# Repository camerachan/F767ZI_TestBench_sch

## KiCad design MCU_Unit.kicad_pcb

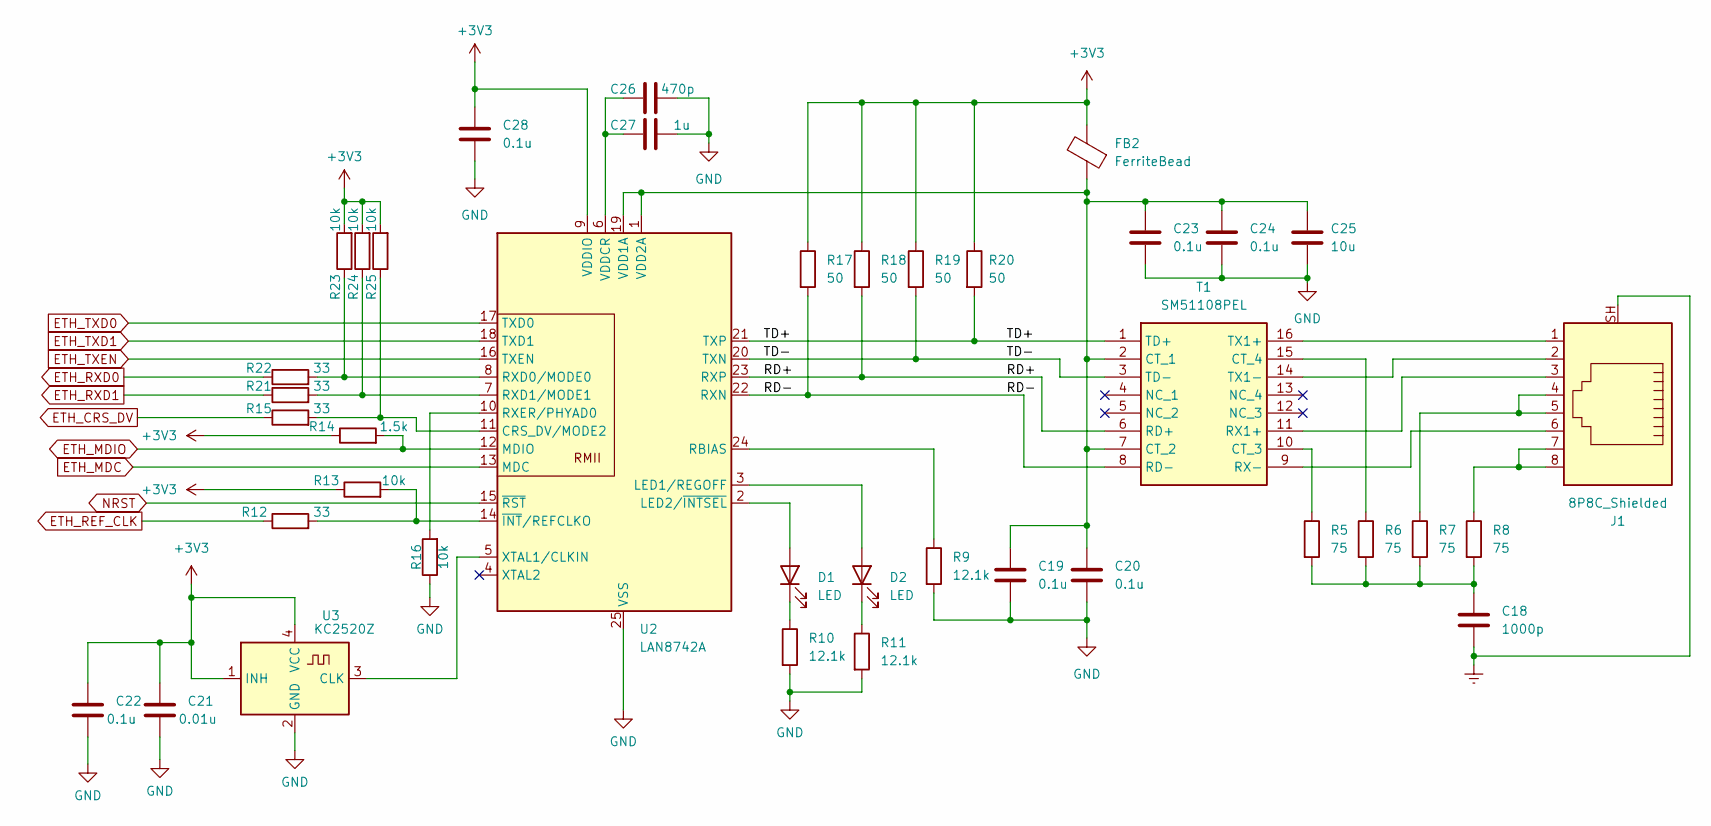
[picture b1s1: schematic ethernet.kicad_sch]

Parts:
C18: 1000p; C_1206_3216Metric_Pad1.33x1.80mm_HandSolder
C19, C20, C22, C23, C24: 0.1u; C_0603_1608Metric_Pad1.08x0.95mm_HandSolder
C21: 0.01u; C_0603_1608Metric_Pad1.08x0.95mm_HandSolder
C25: 10u; C_1206_3216Metric_Pad1.33x1.80mm_HandSolder
C26: 470p; C_0603_1608Metric_Pad1.08x0.95mm_HandSolder
C27: 1u; C_0603_1608Metric_Pad1.08x0.95mm_HandSolder
C28: 0.1u; C_0402_1005Metric_Pad0.74x0.62mm_HandSolder
D1, D2: LED; LED_0603_1608Metric_Pad1.05x0.95mm_HandSolder
FB2: FerriteBead; L_0603_1608Metric_Pad1.05x0.95mm_HandSolder
J1: 8P8C_Shielded; RJ45_Amphenol_RJHSE5380
R5, R6, R7, R8: 75; R_0603_1608Metric_Pad0.98x0.95mm_HandSolder
R9, R10, R11: 12.1k; R_0603_1608Metric_Pad0.98x0.95mm_HandSolder
R12, R15, R21, R22: 33; R_0603_1608Metric_Pad0.98x0.95mm_HandSolder
R13, R16, R23, R24, R25: 10k; R_0603_1608Metric_Pad0.98x0.95mm_HandSolder
R14: 1.5k; R_0603_1608Metric_Pad0.98x0.95mm_HandSolder
R17, R18, R19, R20: 50; R_0603_1608Metric_Pad0.98x0.95mm_HandSolder
T1: SM51108PEL; SOIC127P930X590-16N; Mouser Part Number 652-SM51108PEL
U2: LAN8742A; VQFN-24-1EP_4x4mm_P0.5mm_EP2.45x2.45mm
U3: KC2520Z; Oscillator_SMD_Kyocera_KC2520Z-4Pin_2.5x2.0mm

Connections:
+3V3: C21.1, C22.1, C28.1, FB2.2, R13.1, R14.1, R17.1, R18.1, R19.1, R20.1, R23.2, R24.2, R25.2, U2.9 (VDDIO), U3.1 (INH), U3.4 (VCC); also elsewhere on the board
/Ethernet/RD+: R18.2, T1.6 (RD+), U2.23 (RXP)
/Ethernet/RD-: R17.2, T1.8 (RD-), U2.22 (RXN)
/Ethernet/TD+: R20.2, T1.1 (TD+), U2.21 (TXP)
/Ethernet/TD-: R19.2, T1.3 (TD-), U2.20 (TXN)
ETH_CRS_DV: R15.1; also elsewhere on the board
ETH_MDC: U2.13 (MDC); also elsewhere on the board
ETH_MDIO: R14.2, U2.12 (MDIO); also elsewhere on the board
ETH_REF_CLK: R12.1; also elsewhere on the board
ETH_RXD0: R22.1; also elsewhere on the board
ETH_RXD1: R21.1; also elsewhere on the board
ETH_TXD0: U2.17 (TXD0); also elsewhere on the board
ETH_TXD1: U2.18 (TXD1); also elsewhere on the board
ETH_TXEN: U2.16 (TXEN); also elsewhere on the board
Earth: C18.2, J1.SH
GND: C19.2, C20.2, C21.2, C22.2, C23.2, C24.2, C25.2, C26.2, C27.2, C28.2, R9.2, R10.2, R11.2, R16.1, U2.25 (VSS), U3.2 (GND); also elsewhere on the board
NRST: U2.15 (~RST); also elsewhere on the board
unnamed: C18.1, R5.2, R6.2, R7.2, R8.2
unnamed: D1.2 (A), U2.2 (LED2/~INTSEL)
unnamed: D1.1 (K), R10.1
unnamed: D2.2 (A), U2.3 (LED1/REGOFF)
unnamed: D2.1 (K), R11.1
unnamed: J1.4, J1.5, R7.1
unnamed: J1.7, J1.8, R8.1
unnamed: C19.1, C20.1, C23.1, C24.1, C25.1, FB2.1, T1.2 (CT_1), T1.7 (CT_2), U2.1 (VDD2A), U2.19 (VDD1A)
unnamed: R5.1, T1.10 (CT_3)
unnamed: R6.1, T1.15 (CT_4)
unnamed: J1.3, T1.11 (RX1+)
unnamed: J1.6, T1.9 (RX-)
unnamed: J1.1, T1.16 (TX1+)
unnamed: J1.2, T1.14 (TX1-)
unnamed: R15.2, R25.1, U2.11 (CRS_DV/MODE2)
unnamed: R9.1, U2.24 (RBIAS)
unnamed: R22.2, R23.1, U2.8 (RXD0/MODE0)
unnamed: R21.2, R24.1, U2.7 (RXD1/MODE1)
unnamed: R16.2, U2.10 (RXER/PHYAD0)
unnamed: C26.1, C27.1, U2.6 (VDDCR)
unnamed: U2.5 (XTAL1/CLKIN), U3.3 (CLK)
unnamed: R12.2, R13.2, U2.14 (~INT/REFCLKO)

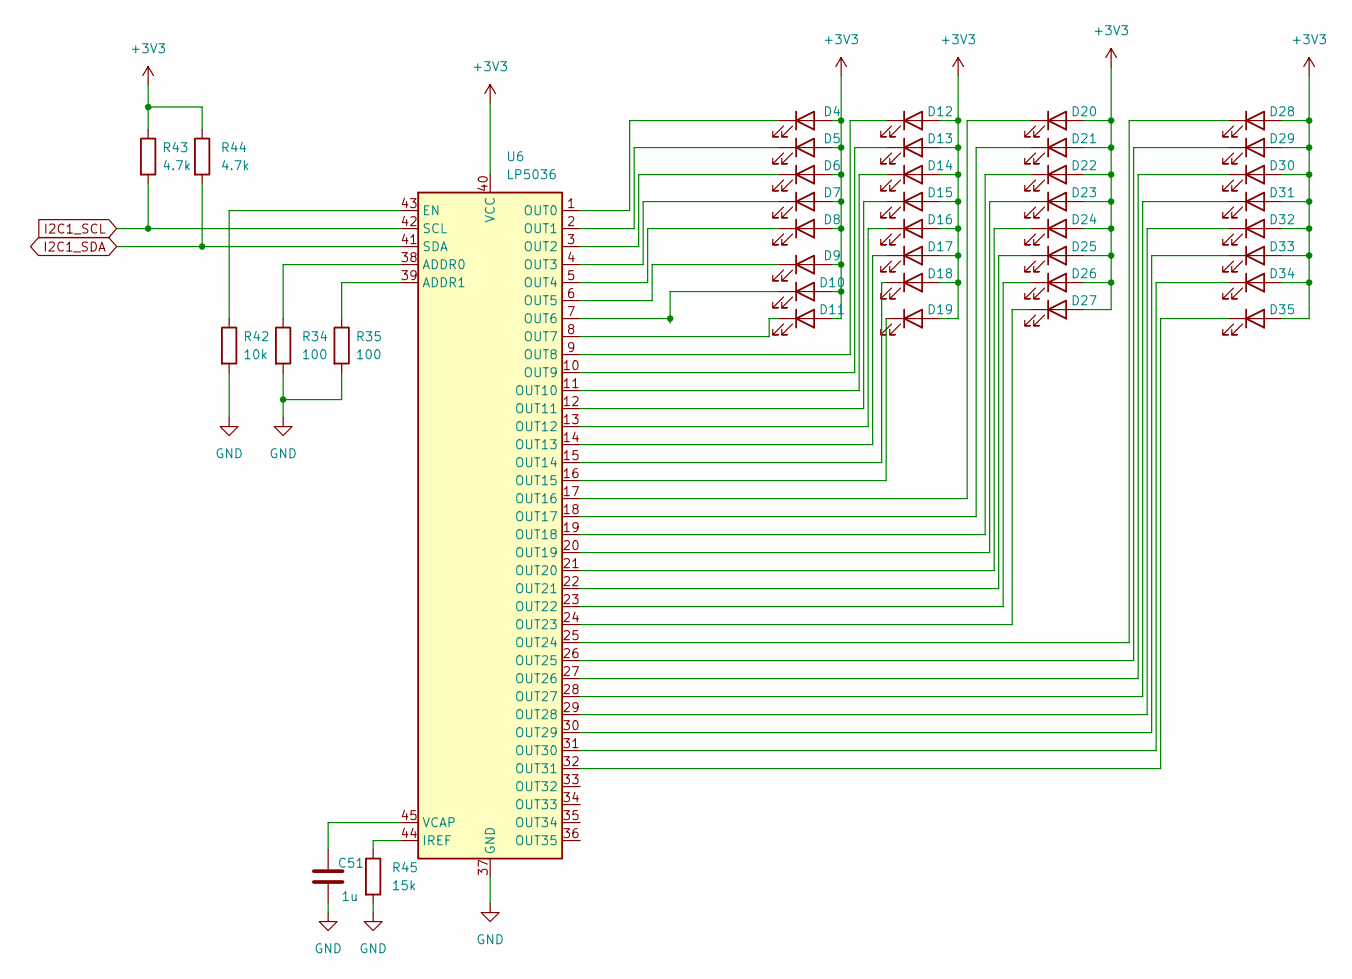
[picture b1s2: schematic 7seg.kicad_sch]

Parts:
C51: 1u; C_0603_1608Metric_Pad1.08x0.95mm_HandSolder
D4, D5, D6, D7, D8, D9, D10, D11, D12, D13, D14, D15, D16, D17, D18, D19, D20, D21, D22, D23, D24, D25, D26, D27, D28, D29, D30, D31, D32, D33, D34, D35: LED; LED_0402_1005Metric_Pad0.77x0.64mm_HandSolder
R34, R35: 100; R_0603_1608Metric_Pad0.98x0.95mm_HandSolder
R42: 10k; R_0603_1608Metric_Pad0.98x0.95mm_HandSolder
R43, R44: 4.7k; R_0603_1608Metric_Pad0.98x0.95mm_HandSolder
R45: 15k; R_0603_1608Metric_Pad0.98x0.95mm_HandSolder
U6: LP5036; VQFN-46-1EP_5x6mm_P0.4mm_EP2.8x3.8mm

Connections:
+3V3: D4.2 (A), D5.2 (A), D6.2 (A), D7.2 (A), D8.2 (A), D9.2 (A), D10.2 (A), D11.2 (A), D12.2 (A), D13.2 (A), D14.2 (A), D15.2 (A), D16.2 (A), D17.2 (A), D18.2 (A), D19.2 (A), D20.2 (A), D21.2 (A), D22.2 (A), D23.2 (A), D24.2 (A), D25.2 (A), D26.2 (A), D27.2 (A), D28.2 (A), D29.2 (A), D30.2 (A), D31.2 (A), D32.2 (A), D33.2 (A), D34.2 (A), D35.2 (A), R43.1, R44.1, U6.40 (VCC); also elsewhere on the board
GND: C51.2, R34.2, R35.2, R42.2, R45.2, U6.37 (GND), U6.46 (GND), U6.47 (GND); also elsewhere on the board
I2C1_SCL: R43.2, U6.42 (SCL); also elsewhere on the board
I2C1_SDA: R44.2, U6.41 (SDA); also elsewhere on the board
unnamed: D4.1 (K), U6.1 (OUT0)
unnamed: D5.1 (K), U6.2 (OUT1)
unnamed: D6.1 (K), U6.3 (OUT2)
unnamed: D7.1 (K), U6.4 (OUT3)
unnamed: D8.1 (K), U6.5 (OUT4)
unnamed: D9.1 (K), U6.6 (OUT5)
unnamed: D10.1 (K), U6.7 (OUT6)
unnamed: D11.1 (K), U6.8 (OUT7)
unnamed: D12.1 (K), U6.9 (OUT8)
unnamed: D13.1 (K), U6.10 (OUT9)
unnamed: D14.1 (K), U6.11 (OUT10)
unnamed: D15.1 (K), U6.12 (OUT11)
unnamed: D16.1 (K), U6.13 (OUT12)
unnamed: D17.1 (K), U6.14 (OUT13)
unnamed: D18.1 (K), U6.15 (OUT14)
unnamed: D19.1 (K), U6.16 (OUT15)
unnamed: D20.1 (K), U6.17 (OUT16)
unnamed: D21.1 (K), U6.18 (OUT17)
unnamed: D22.1 (K), U6.19 (OUT18)
unnamed: D23.1 (K), U6.20 (OUT19)
unnamed: D24.1 (K), U6.21 (OUT20)
unnamed: D25.1 (K), U6.22 (OUT21)
unnamed: D26.1 (K), U6.23 (OUT22)
unnamed: D27.1 (K), U6.24 (OUT23)
unnamed: D28.1 (K), U6.25 (OUT24)
unnamed: D29.1 (K), U6.26 (OUT25)
unnamed: D30.1 (K), U6.27 (OUT26)
unnamed: D31.1 (K), U6.28 (OUT27)
unnamed: D32.1 (K), U6.29 (OUT28)
unnamed: D33.1 (K), U6.30 (OUT29)
unnamed: D34.1 (K), U6.31 (OUT30)
unnamed: D35.1 (K), U6.32 (OUT31)
unnamed: R34.1, U6.38 (ADDR0)
unnamed: R35.1, U6.39 (ADDR1)
unnamed: R42.1, U6.43 (EN)
unnamed: R45.1, U6.44 (IREF)
unnamed: C51.1, U6.45 (VCAP)

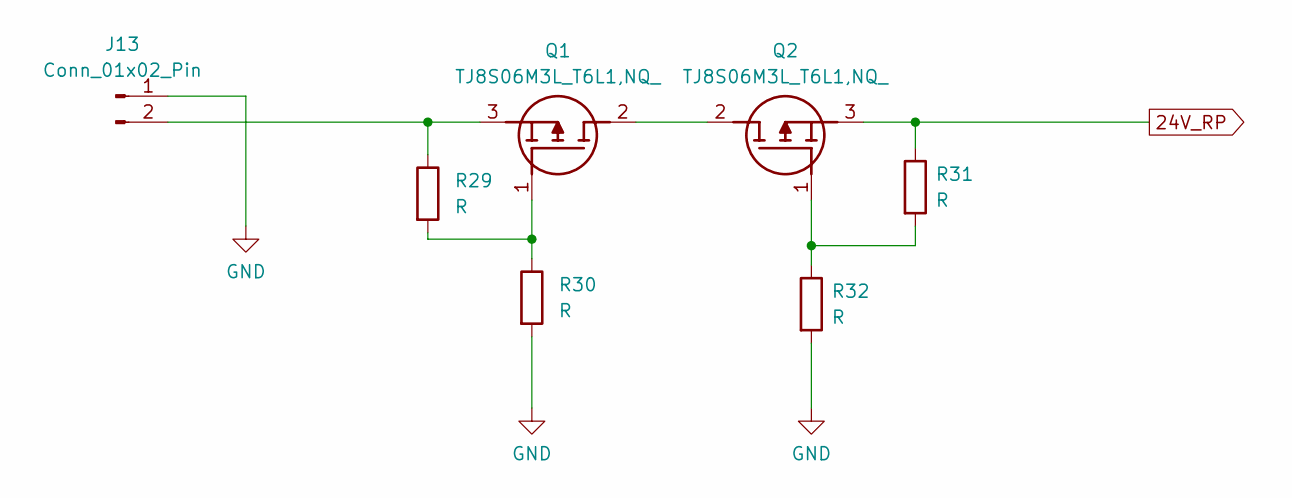
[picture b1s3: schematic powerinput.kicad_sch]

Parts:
J13: Conn_01x02_Pin; AMASS_XT30PW-M_1x02_P2.50mm_Horizontal
Q1, Q2: TJ8S06M3L_T6L1,NQ_; TJ8S06M3LT6L1NQ; Mouser Part Number 757-TJ8S06M3LT6L1NQ
R29, R30, R31, R32: R; R_0603_1608Metric_Pad0.98x0.95mm_HandSolder

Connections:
24V_RP: Q2.3 (S), R31.1; also elsewhere on the board
GND: J13.1, R30.2, R32.2; also elsewhere on the board
unnamed: J13.2, Q1.3 (S), R29.1
unnamed: Q1.2 (D), Q2.2 (D)
unnamed: Q1.1 (G), R29.2, R30.1
unnamed: Q2.1 (G), R31.2, R32.1

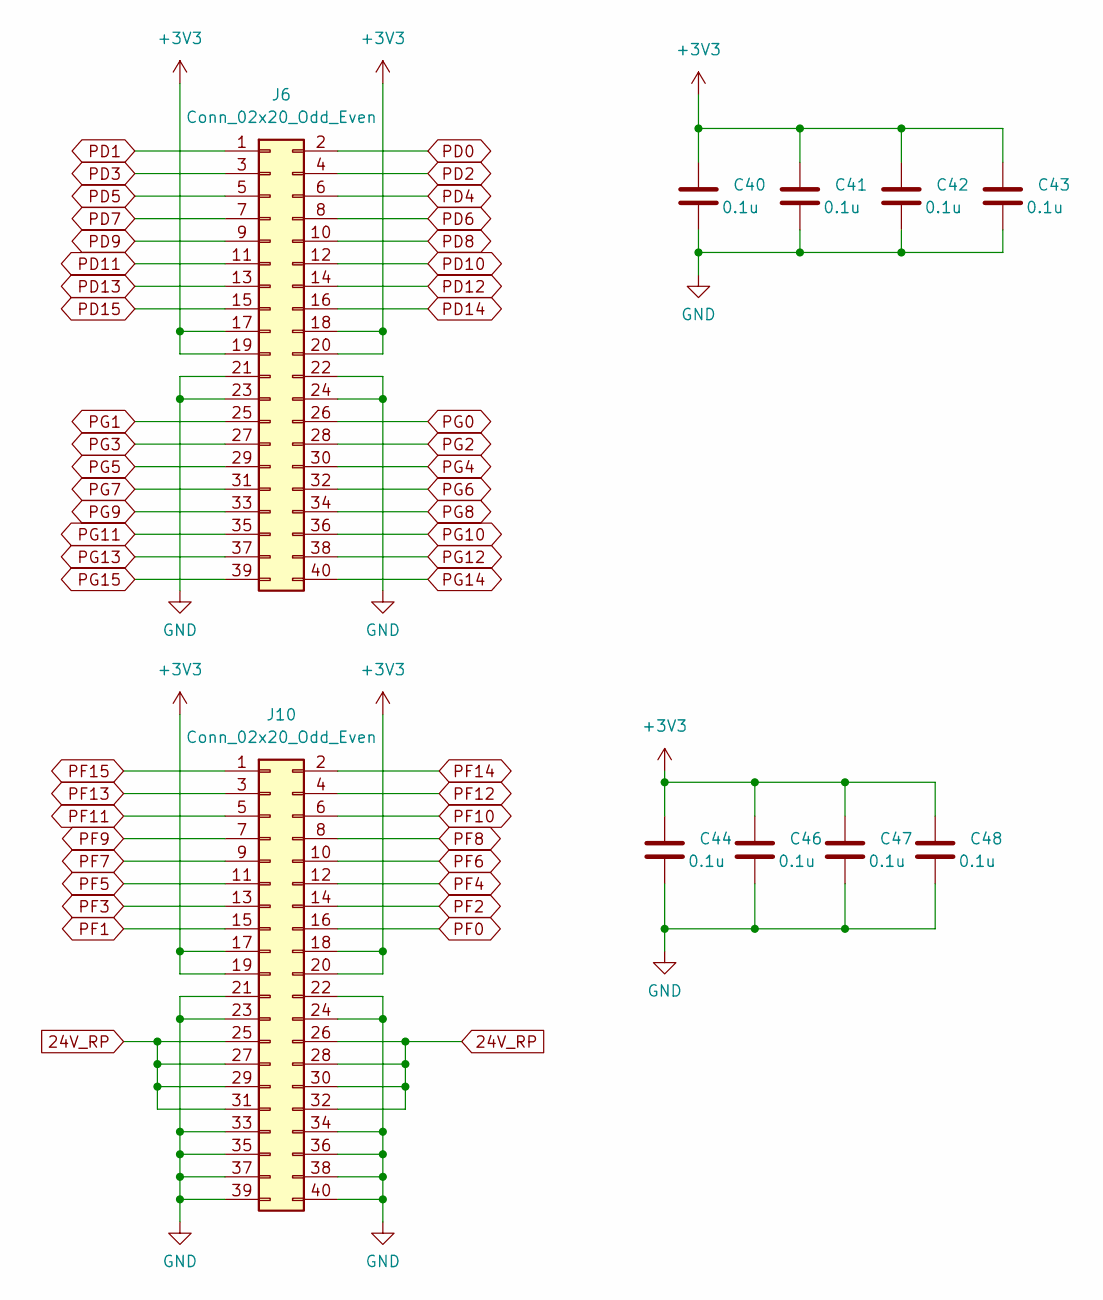
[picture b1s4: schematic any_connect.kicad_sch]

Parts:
C40, C41, C42, C43, C44, C46, C47, C48: 0.1u; C_0603_1608Metric_Pad1.08x0.95mm_HandSolder
J6, J10: Conn_02x20_Odd_Even; PinSocket_2x20_P2.54mm_Vertical

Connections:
24V_RP: J10.25, J10.26, J10.27, J10.28, J10.29, J10.30, J10.31, J10.32; also elsewhere on the board
+3V3: C40.1, C41.1, C42.1, C43.1, C44.1, C46.1, C47.1, C48.1, J6.17, J6.18, J6.19, J6.20, J10.17, J10.18, J10.19, J10.20; also elsewhere on the board
GND: C40.2, C41.2, C42.2, C43.2, C44.2, C46.2, C47.2, C48.2, J6.21, J6.22, J6.23, J6.24, J10.21, J10.22, J10.23, J10.24, J10.33, J10.34, J10.35, J10.36, J10.37, J10.38, J10.39, J10.40; also elsewhere on the board
PD0: J6.2; also elsewhere on the board
PD1: J6.1; also elsewhere on the board
PD2: J6.4; also elsewhere on the board
PD3: J6.3; also elsewhere on the board
PD4: J6.6; also elsewhere on the board
PD5: J6.5; also elsewhere on the board
PD6: J6.8; also elsewhere on the board
PD7: J6.7; also elsewhere on the board
PD8: J6.10; also elsewhere on the board
PD9: J6.9; also elsewhere on the board
PD10: J6.12; also elsewhere on the board
PD11: J6.11; also elsewhere on the board
PD12: J6.14; also elsewhere on the board
PD13: J6.13; also elsewhere on the board
PD14: J6.16; also elsewhere on the board
PD15: J6.15; also elsewhere on the board
PF0: J10.16; also elsewhere on the board
PF1: J10.15; also elsewhere on the board
PF2: J10.14; also elsewhere on the board
PF3: J10.13; also elsewhere on the board
PF4: J10.12; also elsewhere on the board
PF5: J10.11; also elsewhere on the board
PF6: J10.10; also elsewhere on the board
PF7: J10.9; also elsewhere on the board
PF8: J10.8; also elsewhere on the board
PF9: J10.7; also elsewhere on the board
PF10: J10.6; also elsewhere on the board
PF11: J10.5; also elsewhere on the board
PF12: J10.4; also elsewhere on the board
PF13: J10.3; also elsewhere on the board
PF14: J10.2; also elsewhere on the board
PF15: J10.1; also elsewhere on the board
PG0: J6.26; also elsewhere on the board
PG1: J6.25; also elsewhere on the board
PG2: J6.28; also elsewhere on the board
PG3: J6.27; also elsewhere on the board
PG4: J6.30; also elsewhere on the board
PG5: J6.29; also elsewhere on the board
PG6: J6.32; also elsewhere on the board
PG7: J6.31; also elsewhere on the board
PG8: J6.34; also elsewhere on the board
PG9: J6.33; also elsewhere on the board
PG10: J6.36; also elsewhere on the board
PG11: J6.35; also elsewhere on the board
PG12: J6.38; also elsewhere on the board
PG13: J6.37; also elsewhere on the board
PG14: J6.40; also elsewhere on the board
PG15: J6.39; also elsewhere on the board

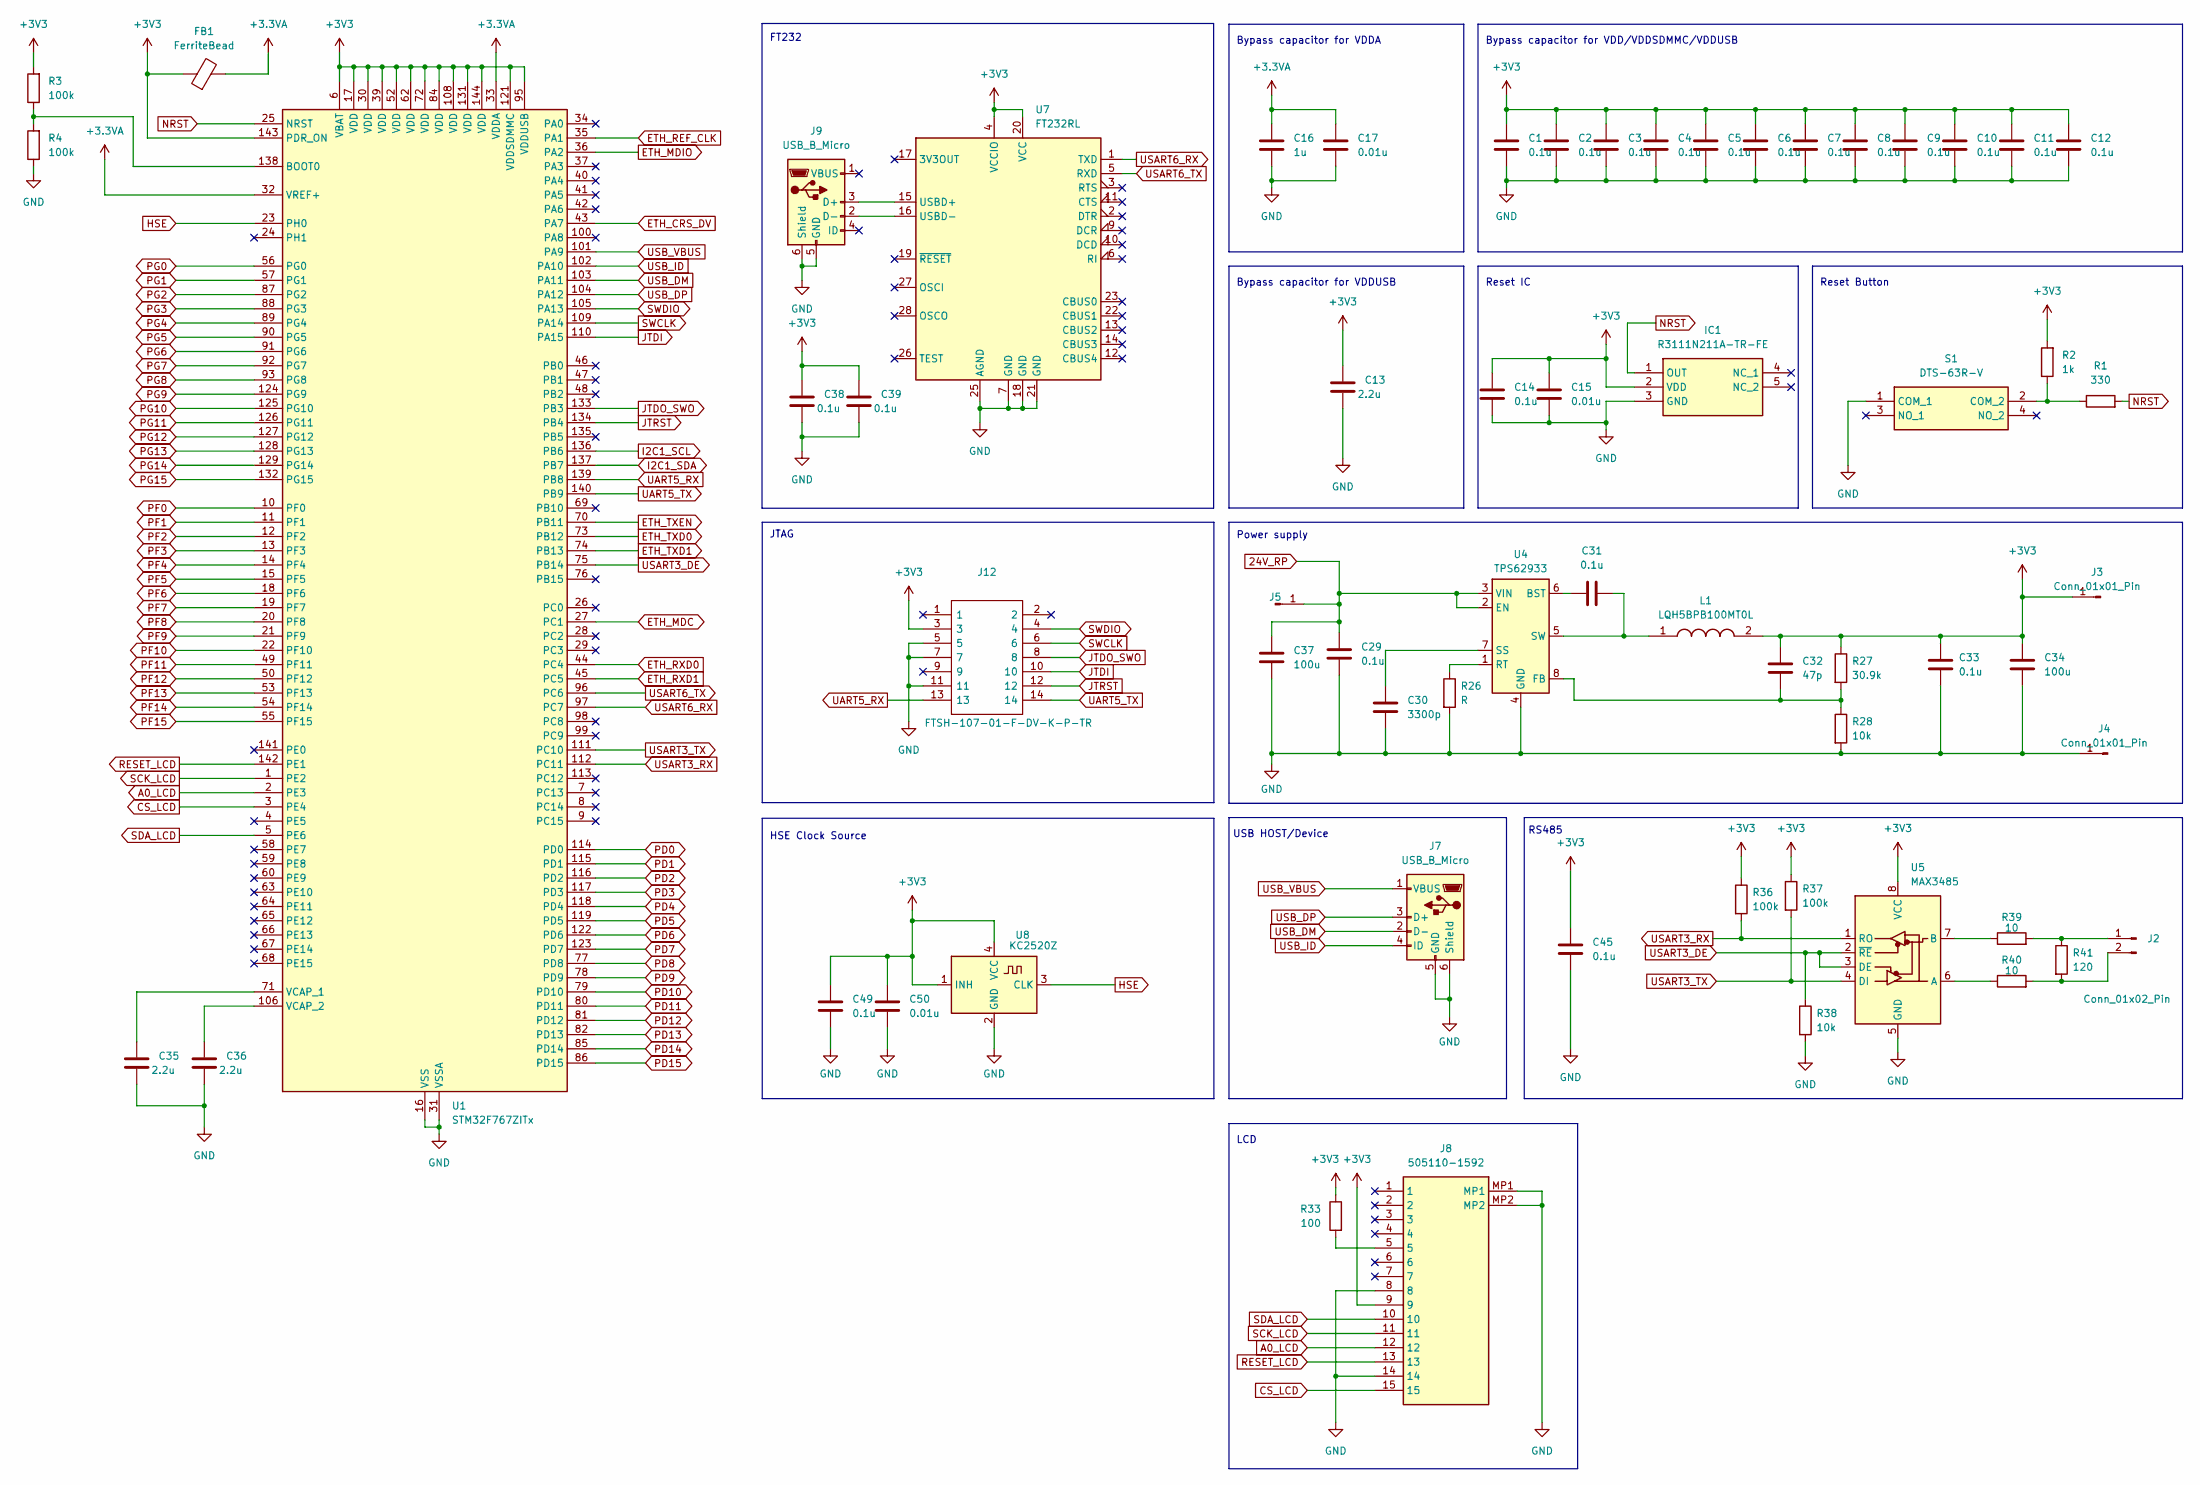
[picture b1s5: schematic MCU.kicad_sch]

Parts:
C1, C2, C3, C4, C5, C6, C7, C8, C9, C10, C11, C12, C14, C49: 0.1u; C_0402_1005Metric_Pad0.74x0.62mm_HandSolder
C13, C35, C36: 2.2u; C_0603_1608Metric_Pad1.08x0.95mm_HandSolder
C15, C17, C50: 0.01u; C_0402_1005Metric_Pad0.74x0.62mm_HandSolder
C16: 1u; C_0402_1005Metric_Pad0.74x0.62mm_HandSolder
C29, C31, C33, C38, C39, C45: 0.1u; C_0603_1608Metric_Pad1.08x0.95mm_HandSolder
C30: 3300p; C_0603_1608Metric_Pad1.08x0.95mm_HandSolder
C32: 47p; C_0603_1608Metric_Pad1.08x0.95mm_HandSolder
C34, C37: 100u; C_Elec_8x10.2
FB1: FerriteBead; L_0603_1608Metric_Pad1.05x0.95mm_HandSolder
IC1: R3111N211A-TR-FE; SOT95P280X130-5N; Mouser Part Number 848-R3111N211A-TR-FE
J2: Conn_01x02_Pin; JST_XH_B2B-XH-AM_1x02_P2.50mm_Vertical
J3, J4, J5: Conn_01x01_Pin; PinHeader_1x01_P2.54mm_Vertical
J7, J9: USB_B_Micro; USB_Mini-B_Wuerth_65100516121_Horizontal
J8: 505110-1592; 5051101592; Mouser Part Number 538-505110-1592
J12: FTSH-107-01-F-DV-K-P-TR; FTSH-107-XX-YYY-DV-K-P-TR; Mouser Part Number 200-FTSH10701FDVKPTR
L1: LQH5BPB100MT0L; Mouser Part Number 81-LQH5BPB100MT0L
R1: 330; R_0603_1608Metric_Pad0.98x0.95mm_HandSolder
R2: 1k; R_0603_1608Metric_Pad0.98x0.95mm_HandSolder
R3, R4, R36, R37: 100k; R_0603_1608Metric_Pad0.98x0.95mm_HandSolder
R26: R; R_0603_1608Metric_Pad0.98x0.95mm_HandSolder
R27: 30.9k; R_0603_1608Metric_Pad0.98x0.95mm_HandSolder
R28, R38: 10k; R_0603_1608Metric_Pad0.98x0.95mm_HandSolder
R33: 100; R_0603_1608Metric_Pad0.98x0.95mm_HandSolder
R39, R40: 10; R_0603_1608Metric_Pad0.98x0.95mm_HandSolder
R41: 120; R_Axial_DIN0207_L6.3mm_D2.5mm_P10.16mm_Horizontal
S1: DTS-63R-V; DTS63RV; Mouser Part Number 113-DTS63RV
U1: STM32F767ZITx; LQFP-144_20x20mm_P0.5mm
U4: TPS62933; SOT-583-8
U5: MAX3485; SOIC-8_3.9x4.9mm_P1.27mm
U7: FT232RL; SSOP-28_5.3x10.2mm_P0.65mm
U8: KC2520Z; Oscillator_SMD_Kyocera_KC2520Z-4Pin_2.5x2.0mm

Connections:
24V_RP: C29.1, C37.1, J5.1, U4.2 (EN), U4.3 (VIN); also elsewhere on the board
+3.3VA: C16.1, C17.1, FB1.2, U1.32 (VREF+), U1.33 (VDDA)
+3V3: C1.1, C2.1, C3.1, C4.1, C5.1, C6.1, C7.1, C8.1, C9.1, C10.1, C11.1, C12.1, C13.1, C14.1, C15.1, C32.1, C33.1, C34.1, C38.1, C39.1, C45.1, C49.1, C50.1, FB1.1, IC1.2 (VDD), J3.1, J8.9, J12.3, L1.2, R2.2, R3.2, R27.1, R33.1, R36.1, R37.1, U1.6 (VBAT), U1.17 (VDD), U1.30 (VDD), U1.39 (VDD), U1.52 (VDD), U1.62 (VDD), U1.72 (VDD), U1.84 (VDD), U1.95 (VDDUSB), U1.108 (VDD), U1.121 (VDDSDMMC), U1.131 (VDD), U1.143 (PDR_ON), U1.144 (VDD), U5.8 (VCC), U7.4 (VCCIO), U7.20 (VCC), U8.1 (INH), U8.4 (VCC); also elsewhere on the board
A0_LCD: J8.12, U1.2 (PE3)
CS_LCD: J8.15, U1.3 (PE4)
ETH_CRS_DV: U1.43 (PA7); also elsewhere on the board
ETH_MDC: U1.27 (PC1); also elsewhere on the board
ETH_MDIO: U1.36 (PA2); also elsewhere on the board
ETH_REF_CLK: U1.35 (PA1); also elsewhere on the board
ETH_RXD0: U1.44 (PC4); also elsewhere on the board
ETH_RXD1: U1.45 (PC5); also elsewhere on the board
ETH_TXD0: U1.73 (PB12); also elsewhere on the board
ETH_TXD1: U1.74 (PB13); also elsewhere on the board
ETH_TXEN: U1.70 (PB11); also elsewhere on the board
GND: C1.2, C2.2, C3.2, C4.2, C5.2, C6.2, C7.2, C8.2, C9.2, C10.2, C11.2, C12.2, C13.2, C14.2, C15.2, C16.2, C17.2, C29.2, C30.2, C33.2, C34.2, C35.2, C36.2, C37.2, C38.2, C39.2, C45.2, C49.2, C50.2, IC1.3 (GND), J4.1, J7.5 (GND), J7.6 (Shield), J8.8, J8.14, J8.MP1, J8.MP2, J9.5 (GND), J9.6 (Shield), J12.5, J12.7, J12.11, R4.1, R26.2, R28.2, R38.2, S1.1 (COM), U1.16 (VSS), U1.31 (VSSA), U1.38 (VSS), U1.51 (VSS), U1.61 (VSS), U1.83 (VSS), U1.94 (VSS), U1.107 (VSS), U1.120 (VSS), U1.130 (VSS), U4.4 (GND), U5.5 (GND), U7.7 (GND), U7.18 (GND), U7.21 (GND), U7.25 (AGND), U8.2 (GND); also elsewhere on the board
HSE: U1.23 (PH0), U8.3 (CLK)
I2C1_SCL: U1.136 (PB6); also elsewhere on the board
I2C1_SDA: U1.137 (PB7); also elsewhere on the board
JTDI: J12.10, U1.110 (PA15)
JTDO_SWO: J12.8, U1.133 (PB3)
JTRST: J12.12, U1.134 (PB4)
NRST: IC1.1 (OUT), R1.2, U1.25 (NRST); also elsewhere on the board
unnamed: J2.1, R39.2, R41.1
unnamed: J2.2, R40.2, R41.2
unnamed: J8.5, R33.2
unnamed: J9.3 (D+), U7.15 (USBD+)
unnamed: J9.2 (D-), U7.16 (USBD-)
unnamed: R1.1, R2.1, S1.2 (COM)
unnamed: R3.1, R4.2, U1.138 (BOOT0)
unnamed: C35.1, U1.71 (VCAP_1)
unnamed: C36.1, U1.106 (VCAP_2)
unnamed: C31.1, U4.6 (BST)
unnamed: C32.2, R27.2, R28.1, U4.8 (FB)
unnamed: R26.1, U4.1 (RT)
unnamed: C30.1, U4.7 (SS)
unnamed: C31.2, L1.1, U4.5 (SW)
unnamed: R40.1, U5.6 (A)
unnamed: R39.1, U5.7 (B)
PD0: U1.114 (PD0); also elsewhere on the board
PD1: U1.115 (PD1); also elsewhere on the board
PD2: U1.116 (PD2); also elsewhere on the board
PD3: U1.117 (PD3); also elsewhere on the board
PD4: U1.118 (PD4); also elsewhere on the board
PD5: U1.119 (PD5); also elsewhere on the board
PD6: U1.122 (PD6); also elsewhere on the board
PD7: U1.123 (PD7); also elsewhere on the board
PD8: U1.77 (PD8); also elsewhere on the board
PD9: U1.78 (PD9); also elsewhere on the board
PD10: U1.79 (PD10); also elsewhere on the board
PD11: U1.80 (PD11); also elsewhere on the board
PD12: U1.81 (PD12); also elsewhere on the board
PD13: U1.82 (PD13); also elsewhere on the board
PD14: U1.85 (PD14); also elsewhere on the board
PD15: U1.86 (PD15); also elsewhere on the board
PF0: U1.10 (PF0); also elsewhere on the board
PF1: U1.11 (PF1); also elsewhere on the board
PF2: U1.12 (PF2); also elsewhere on the board
PF3: U1.13 (PF3); also elsewhere on the board
PF4: U1.14 (PF4); also elsewhere on the board
PF5: U1.15 (PF5); also elsewhere on the board
PF6: U1.18 (PF6); also elsewhere on the board
PF7: U1.19 (PF7); also elsewhere on the board
PF8: U1.20 (PF8); also elsewhere on the board
PF9: U1.21 (PF9); also elsewhere on the board
PF10: U1.22 (PF10); also elsewhere on the board
PF11: U1.49 (PF11); also elsewhere on the board
PF12: U1.50 (PF12); also elsewhere on the board
PF13: U1.53 (PF13); also elsewhere on the board
PF14: U1.54 (PF14); also elsewhere on the board
PF15: U1.55 (PF15); also elsewhere on the board
PG0: U1.56 (PG0); also elsewhere on the board
PG1: U1.57 (PG1); also elsewhere on the board
PG2: U1.87 (PG2); also elsewhere on the board
PG3: U1.88 (PG3); also elsewhere on the board
PG4: U1.89 (PG4); also elsewhere on the board
PG5: U1.90 (PG5); also elsewhere on the board
PG6: U1.91 (PG6); also elsewhere on the board
PG7: U1.92 (PG7); also elsewhere on the board
PG8: U1.93 (PG8); also elsewhere on the board
PG9: U1.124 (PG9); also elsewhere on the board
PG10: U1.125 (PG10); also elsewhere on the board
PG11: U1.126 (PG11); also elsewhere on the board
PG12: U1.127 (PG12); also elsewhere on the board
PG13: U1.128 (PG13); also elsewhere on the board
PG14: U1.129 (PG14); also elsewhere on the board
PG15: U1.132 (PG15); also elsewhere on the board
RESET_LCD: J8.13, U1.142 (PE1)
SCK_LCD: J8.11, U1.1 (PE2)
SDA_LCD: J8.10, U1.5 (PE6)
SWCLK: J12.6, U1.109 (PA14)
SWDIO: J12.4, U1.105 (PA13)
UART5_RX: J12.13, U1.139 (PB8)
UART5_TX: J12.14, U1.140 (PB9)
USART3_DE: R38.1, U1.75 (PB14), U5.2 (~RE), U5.3 (DE)
USART3_RX: R36.2, U1.112 (PC11), U5.1 (RO)
USART3_TX: R37.2, U1.111 (PC10), U5.4 (DI)
USART6_RX: U1.97 (PC7), U7.1 (TXD)
USART6_TX: U1.96 (PC6), U7.5 (RXD)
USB_DM: J7.2 (D-), U1.103 (PA11)
USB_DP: J7.3 (D+), U1.104 (PA12)
USB_ID: J7.4 (ID), U1.102 (PA10)
USB_VBUS: J7.1 (VBUS), U1.101 (PA9)

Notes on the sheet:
Reset IC
HSE Clock Source
Bypass capacitor for VDDA
RS485
USB HOST/Device
JTAG
Bypass capacitor for VDDUSB
Bypass capacitor for VDD/VDDSDMMC/VDDUSB
FT232
Power supply
Reset Button
LCD

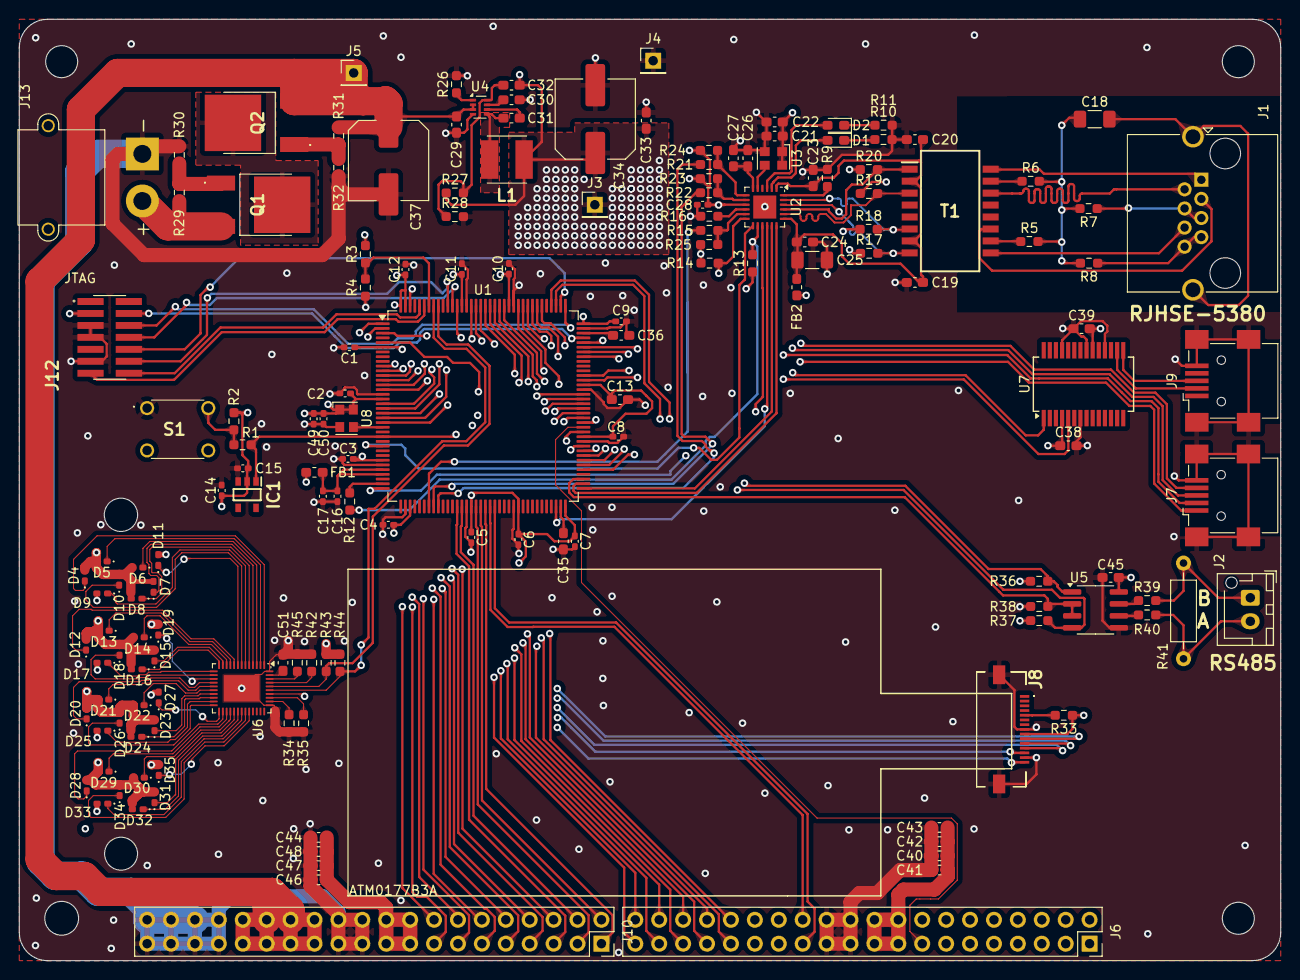
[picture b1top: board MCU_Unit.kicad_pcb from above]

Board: 4 copper layers, 134.0 x 100.0 mm, 158 parts (0 on the bottom side), 170 nets.

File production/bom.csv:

Designator,Footprint,Quantity,Value,LCSC Part #
"C1, C10, C11, C12, C14, C2, C28, C3, C4, C49, C5, C6, C7, C8, C9",0402,15,0.1u,
"C13, C35, C36",0603,3,2.2u,
"C15, C17, C50",0402,3,0.01u,
C16,0402,1,1u,
C18,1206,1,1000p,
"C19, C20, C22, C23, C24, C29, C31, C33, C38, C39, C40, C41, C42, C43, C44, C45, C46, C47, C48",0603,19,0.1u,
C21,0603,1,0.01u,
C25,1206,1,10u,
C26,0603,1,470p,
"C27, C51",0603,2,1u,
C30,0603,1,3300p,
C32,0603,1,47p,
"C34, C37",C_Elec_8x10.2,2,100u,
"D1, D2",0603,2,LED,
"D10, D11, D12, D13, D14, D15, D16, D17, D18, D19, D20, D21, D22, D23, D24, D25, D26, D27, D28, D29, D30, D31, D32, D33, D34, D35, D4, D5, D6, D7, D8, D9",0402,32,LED,
"FB1, FB2",0603,2,FerriteBead,
IC1,SOT95P280X130-5N,1,R3111N211A-TR-FE,
J1,RJ45_Amphenol_RJHSE5380,1,8P8C_Shielded,
"J10, J6",PinSocket_2x20_P2.54mm_Vertical,2,Conn_02x20_Odd_Even,
J12,FTSH-107-XX-YYY-DV-K-P-TR,1,FTSH-107-01-F-DV-K-P-TR,
J13,AMASS_XT30PW-M_1x02_P2.50mm_Horizontal,1,Conn_01x02_Pin,
J2,JST_XH_B2B-XH-AM_1x02_P2.50mm_Vertical,1,Conn_01x02_Pin,
"J3, J4, J5",PinHeader_1x01_P2.54mm_Vertical,3,Conn_01x01_Pin,
"J7, J9",USB_Mini-B_Wuerth_65100516121_Horizontal,2,USB_B_Micro,
J8,5051101592,1,505110-1592,
L1,LQH5BPB100MT0L,1,LQH5BPB100MT0L,
"Q1, Q2",TJ8S06M3LT6L1NQ,2,"TJ8S06M3L_T6L1,NQ_",
R1,0603,1,330,
"R10, R11, R9",0603,3,12.1k,
"R12, R15, R21, R22",0603,4,33,
"R13, R16, R23, R24, R25, R28, R38, R42",0603,8,10k,
R14,0603,1,1.5k,
"R17, R18, R19, R20",0603,4,50,
R2,0603,1,1k,
"R26, R29, R30, R31, R32",0603,5,R,
R27,0603,1,30.9k,
"R3, R36, R37, R4",0603,4,100k,
"R33, R34, R35",0603,3,100,
"R39, R40",0603,2,10,
R41,R_Axial_DIN0207_L6.3mm_D2.5mm_P10.16mm_Horizontal,1,120,
"R43, R44",0603,2,4.7k,
R45,0603,1,15k,
"R5, R6, R7, R8",0603,4,75,
S1,DTS63RV,1,DTS-63R-V,
T1,SOIC127P930X590-16N,1,SM51108PEL,
U1,LQFP-144_20x20mm_P0.5mm,1,STM32F767ZITx,
U2,VQFN-24-1EP_4x4mm_P0.5mm_EP2.45x2.45mm,1,LAN8742A,
"U3, U8",Oscillator_SMD_Kyocera_KC2520Z-4Pin_2.5x2.0mm,2,KC2520Z,
U4,SOT-583-8,1,TPS62933,
U5,SOIC-8_3.9x4.9mm_P1.27mm,1,MAX3485,
U6,VQFN-46-1EP_5x6mm_P0.4mm_EP2.8x3.8mm,1,LP5036,
U7,SSOP-28_5.3x10.2mm_P0.65mm,1,FT232RL,

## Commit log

2024-10-02 fist_commit
